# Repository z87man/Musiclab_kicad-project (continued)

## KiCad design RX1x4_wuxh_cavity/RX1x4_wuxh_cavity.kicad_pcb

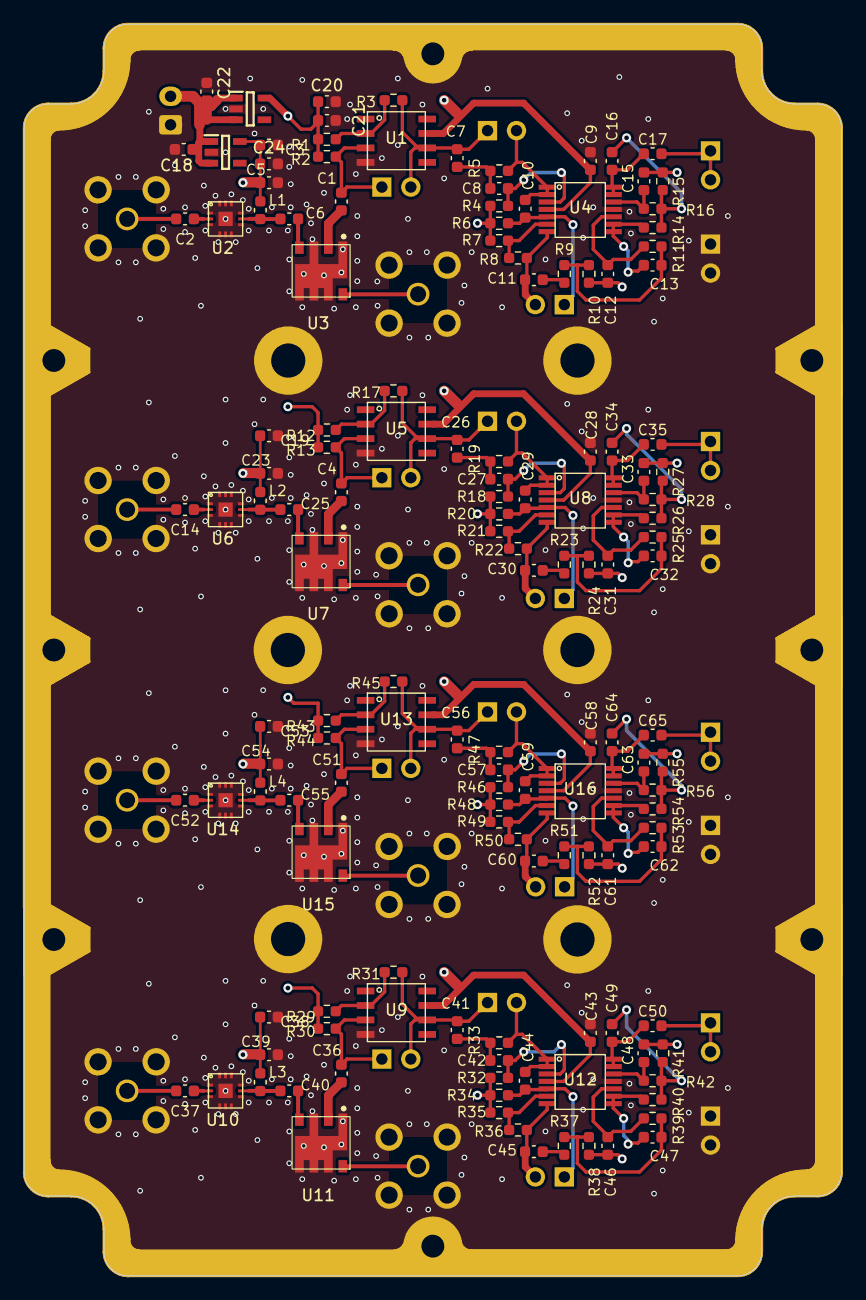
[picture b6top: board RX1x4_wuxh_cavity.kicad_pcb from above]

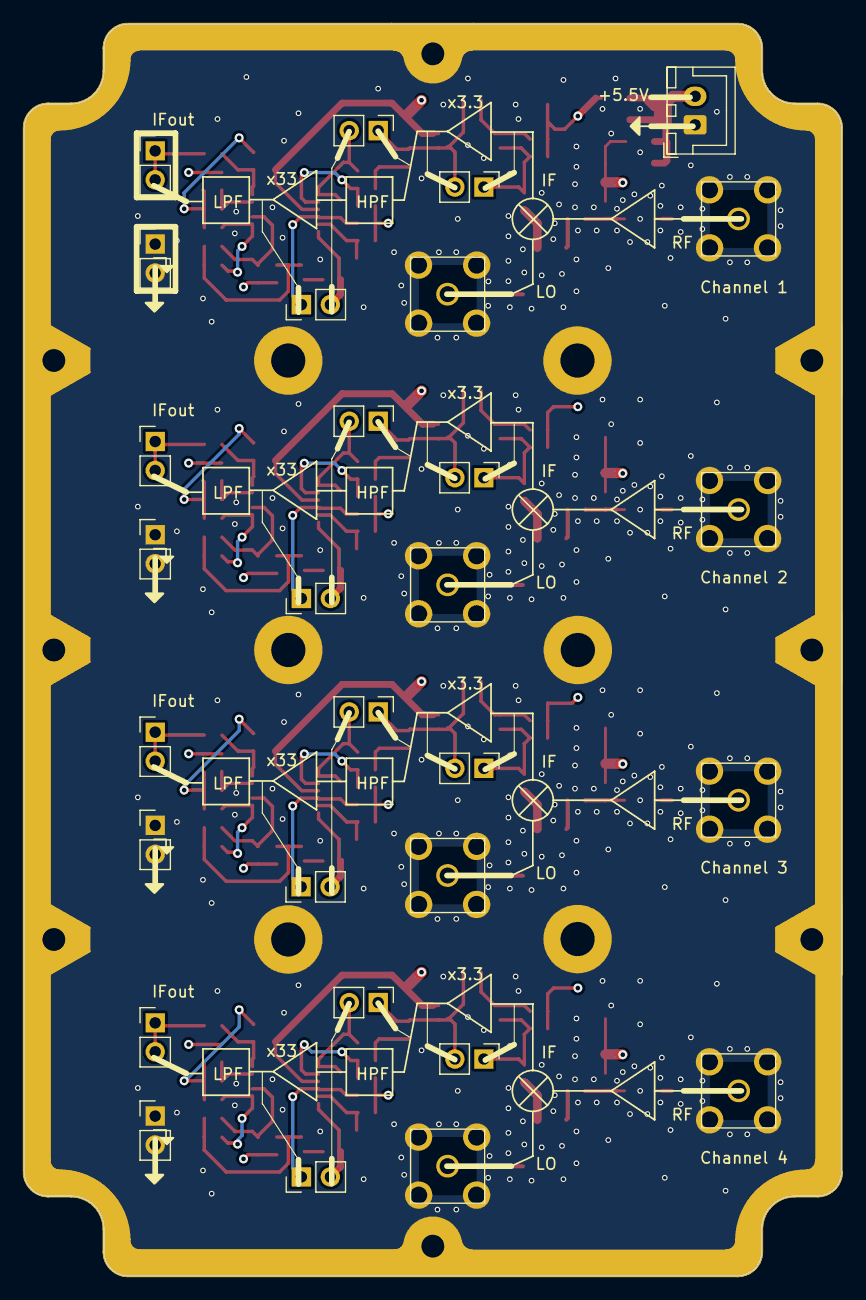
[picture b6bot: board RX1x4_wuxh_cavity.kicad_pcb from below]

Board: 4 copper layers, 71.7 x 109.8 mm, 173 parts (29 on the bottom side), 96 nets.

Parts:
C1, C4, C10, C11, C17, C29, C30, C35, C36, C44, C45, C50, C51, C59, C60, C65: 1u; C_0603_1608Metric_revised
C2, C6, C14, C25, C37, C40, C52, C55: 22 uF; C_0603_1608Metric_revised
C3, C19, C38, C53: 4.7 uF; C_0603_1608Metric_revised
C5, C23, C39, C54: 1 nF; C_0603_1608Metric_revised
C7, C26, C41, C56: 200p; C_0603_1608Metric_revised
C8, C27, C42, C57: 110p; C_0603_1608Metric_revised
C9, C28, C43, C58: 2.2u; C_0603_1608Metric_revised
C12, C15, C31, C33, C46, C48, C61, C63: 100p; C_0603_1608Metric_revised
C13, C32, C47, C62: 120p; C_0603_1608Metric_revised
C16, C34, C49, C64: 750p; C_0603_1608Metric_revised
C18, C20, C22, C24: 1uf; C_0603_1608Metric_revised
C21: 4.7uF; C_0603_1608Metric_revised
IC1: TPS7A2025PDBVR; DC_SOT95P280X145-5N
IC2: TPS7A2050PDBVR; DC_SOT95P280X145-5N
J1, J2, J3, J5, J8, J9, J12, J13, J14, J17, J18, J19: Conn_01x02; PinHeader_1x02_P2.54mm_Vertical
J4: Conn_01x02_Pin; JST_XH_B2B-XH-A_1x02_P2.50mm_Vertical
J6, J7, J10, J11, J15, J16, J20, J21: Conn_01x02_Pin; PinHeader_1x02_P2.54mm_Vertical
L1, L2, L3, L4: 15 nH; L_0603_1608Metric_revised
R1, R2, R6, R7, R12, R13, R20, R21, R29, R30, R34, R35, R43, R44, R48, R49: 1k; R_0603_1608Metric_revised
R3, R17, R31, R45: 3.3k; R_0603_1608Metric_revised
R4, R18, R32, R46: 16k; R_0603_1608Metric_revised
R5, R19, R33, R47: 7.5k; R_0603_1608Metric_revised
R8, R22, R36, R50: 33k; R_0603_1608Metric_revised
R9, R23, R37, R51: 6.2k; R_0603_1608Metric_revised
R10, R15, R24, R27, R38, R41, R52, R55: 100k; R_0603_1608Metric_revised
R11, R25, R39, R53: 8.2k; R_0603_1608Metric_revised
R14, R26, R40, R54: 2.2k; R_0603_1608Metric_revised
R16, R28, R42, R56: 3.9k; R_0603_1608Metric_revised
SMA1, SMA2, SMA3, SMA4, SMA5, SMA6, SMA7, SMA8: SMA_KHD
U1, U5, U9, U13: OPA1611_SOIC8; OPA1611-SOIC8
U2, U6, U10, U14: PMA-63GLN+; PMA3-63GLN+
U3, U7, U11, U15: SIM73L
U4, U8, U12, U16: TL974IPWR
outline1: Outline_8x5_cavity_20230723(2mm)

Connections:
+2.5V: C12.2, C15.2, C20.1, C21.1, C31.2, C33.2, C46.2, C48.2, C61.2, C63.2, IC1.5 (OUT), R1.2, R2.2, R4.1, R6.2, R7.2, R10.2, R12.2, R13.2, R15.2, R18.1, R20.2, R21.2, R24.2, R27.2, R29.2, R30.2, R32.1, R34.2, R35.2, R38.2, R41.2, R43.2, R44.2, R46.1, R48.2, R49.2, R52.2, R55.2
+5V: C3.1, C5.1, C9.1, C19.1, C23.1, C24.1, C28.1, C38.1, C39.1, C43.1, C53.1, C54.1, C58.1, IC2.5 (OUT), L1.1, L2.1, L3.1, L4.1, U1.7 (V+), U4.4 (V+), U5.7 (V+), U8.4 (V+), U9.7 (V+), U12.4 (V+), U13.7 (V+), U16.4 (V+)
/RX_singleChannel1/IF: C4.1, U7.2 (IF)
/RX_singleChannel2/IF: C36.1, U11.2 (IF)
/RX_singleChannel3/IF: C51.1, U15.2 (IF)
/RX_singleChannel/IF: C1.1, U3.2 (IF)
GND: C3.2, C5.2, C9.2, C18.2, C19.2, C20.2, C21.2, C22.2, C23.2, C24.2, C28.2, C38.2, C39.2, C43.2, C53.2, C54.2, C58.2, IC1.2 (GND), IC2.2 (GND), J4.1, J7.1, J7.2, J11.1, J11.2, J16.1, J16.2, J21.1, J21.2, SMA1.2, SMA2.2, SMA3.2, SMA4.2, SMA5.2, SMA6.2, SMA7.2, SMA8.2, U1.4 (V-), U2.1 (NC), U2.3 (NC), U2.4 (NC), U2.5 (NC), U2.6 (NC), U2.7 (NC), U2.9 (NC), U2.10 (NC), U2.11 (NC), U2.12 (NC), U2.13 (EP), U3.1 (GND), U3.3 (GND), U3.5 (GND), U3.6 (GND), U3.7 (GND), U3.9 (GND), U4.11 (V-), U5.4 (V-), U6.1 (NC), U6.3 (NC), U6.4 (NC), U6.5 (NC), U6.6 (NC), U6.7 (NC), U6.9 (NC), U6.10 (NC), U6.11 (NC), U6.12 (NC), U6.13 (EP), U7.1 (GND), U7.3 (GND), U7.5 (GND), U7.6 (GND), U7.7 (GND), U7.9 (GND), U8.11 (V-), U9.4 (V-), U10.1 (NC), U10.3 (NC), U10.4 (NC), U10.5 (NC), U10.6 (NC), U10.7 (NC), U10.9 (NC), U10.10 (NC), U10.11 (NC), U10.12 (NC), U10.13 (EP), U11.1 (GND), U11.3 (GND), U11.5 (GND), U11.6 (GND), U11.7 (GND), U11.9 (GND), U12.11 (V-), U13.4 (V-), U14.1 (NC), U14.3 (NC), U14.4 (NC), U14.5 (NC), U14.6 (NC), U14.7 (NC), U14.9 (NC), U14.10 (NC), U14.11 (NC), U14.12 (NC), U14.13 (EP), U15.1 (GND), U15.3 (GND), U15.5 (GND), U15.6 (GND), U15.7 (GND), U15.9 (GND), U16.11 (V-), outline1.1 (GND)
unnamed: C2.1, SMA1.1
unnamed: C7.2, C8.1, R5.1
unnamed: C11.2, R9.1
unnamed: C12.1, R11.2, U4.10 (In)
unnamed: C13.1, R9.2, R10.1, R11.1
unnamed: C14.1, SMA3.1
unnamed: C15.1, R16.2, U4.12 (In)
unnamed: C16.1, R14.2, R15.1, R16.1
unnamed: C26.2, C27.1, R19.1
unnamed: C30.2, R23.1
unnamed: C31.1, R25.2, U8.10 (In)
unnamed: C32.1, R23.2, R24.1, R25.1
unnamed: C33.1, R28.2, U8.12 (In)
unnamed: C34.1, R26.2, R27.1, R28.1
unnamed: C37.1, SMA5.1
unnamed: C41.2, C42.1, R33.1
unnamed: C45.2, R37.1
unnamed: C46.1, R39.2, U12.10 (In)
unnamed: C47.1, R37.2, R38.1, R39.1
unnamed: C48.1, R42.2, U12.12 (In)
unnamed: C49.1, R40.2, R41.1, R42.1
unnamed: C52.1, SMA7.1
unnamed: C56.2, C57.1, R47.1
unnamed: C60.2, R51.1
unnamed: C61.1, R53.2, U16.10 (In)
unnamed: C62.1, R51.2, R52.1, R53.1
unnamed: C63.1, R56.2, U16.12 (In)
unnamed: C64.1, R54.2, R55.1, R56.1
unnamed: C1.2, J1.1, R2.1, U1.3 (in+)
unnamed: C7.1, J1.2, J2.1, R3.2, U1.6 (Out)
unnamed: C10.1, J2.2, R5.2, U4.1 (Out), U4.2 (in-)
unnamed: C10.2, J3.1, R6.1, U4.5 (In)
unnamed: C11.1, J3.2, R8.2, U4.7 (Out)
unnamed: C4.2, J5.1, R13.1, U5.3 (in+)
unnamed: C26.1, J5.2, J8.1, R17.2, U5.6 (Out)
unnamed: C17.2, J6.1, J6.2
unnamed: C29.1, J8.2, R19.2, U8.1 (Out), U8.2 (in-)
unnamed: C29.2, J9.1, R20.1, U8.5 (In)
unnamed: C30.1, J9.2, R22.2, U8.7 (Out)
unnamed: C35.2, J10.1, J10.2
unnamed: C36.2, J12.1, R30.1, U9.3 (in+)
unnamed: C41.1, J12.2, J13.1, R31.2, U9.6 (Out)
unnamed: C44.1, J13.2, R33.2, U12.1 (Out), U12.2 (in-)
unnamed: C44.2, J14.1, R34.1, U12.5 (In)
unnamed: C45.1, J14.2, R36.2, U12.7 (Out)
unnamed: C50.2, J15.1, J15.2
unnamed: C51.2, J17.1, R44.1, U13.3 (in+)
unnamed: C56.1, J17.2, J18.1, R45.2, U13.6 (Out)
unnamed: C59.1, J18.2, R47.2, U16.1 (Out), U16.2 (in-)
unnamed: C59.2, J19.1, R48.1, U16.5 (In)
unnamed: C60.1, J19.2, R50.2, U16.7 (Out)
unnamed: C65.2, J20.1, J20.2
unnamed: R7.1, R8.1, U4.6 (In)
unnamed: R21.1, R22.1, U8.6 (In)
unnamed: R35.1, R36.1, U12.6 (In)
unnamed: R49.1, R50.1, U16.6 (In)
unnamed: R1.1, R3.1, U1.2 (in-)
unnamed: C2.2, U2.2 (RFin)
unnamed: C6.1, L1.2, U2.8 (RFout&DCin)
unnamed: SMA2.1, U3.8 (LO)
unnamed: C6.2, U3.4 (RF)
unnamed: C8.2, R4.2, U4.3 (in+)
unnamed: C13.2, R14.1, U4.8 (Out), U4.9 (In)
unnamed: C16.2, C17.1, U4.13 (In), U4.14 (Out)
unnamed: R12.1, R17.1, U5.2 (in-)
unnamed: C14.2, U6.2 (RFin)
unnamed: C25.1, L2.2, U6.8 (RFout&DCin)
unnamed: SMA4.1, U7.8 (LO)
unnamed: C25.2, U7.4 (RF)
unnamed: C27.2, R18.2, U8.3 (in+)
unnamed: C32.2, R26.1, U8.8 (Out), U8.9 (In)
unnamed: C34.2, C35.1, U8.13 (In), U8.14 (Out)
unnamed: R29.1, R31.1, U9.2 (in-)
unnamed: C37.2, U10.2 (RFin)
unnamed: C40.1, L3.2, U10.8 (RFout&DCin)
unnamed: SMA6.1, U11.8 (LO)
unnamed: C40.2, U11.4 (RF)
unnamed: C42.2, R32.2, U12.3 (in+)
unnamed: C47.2, R40.1, U12.8 (Out), U12.9 (In)
unnamed: C49.2, C50.1, U12.13 (In), U12.14 (Out)
unnamed: R43.1, R45.1, U13.2 (in-)
unnamed: C52.2, U14.2 (RFin)
unnamed: C55.1, L4.2, U14.8 (RFout&DCin)
unnamed: SMA8.1, U15.8 (LO)
unnamed: C55.2, U15.4 (RF)
unnamed: C57.2, R46.2, U16.3 (in+)
unnamed: C62.2, R54.1, U16.8 (Out), U16.9 (In)
unnamed: C64.2, C65.1, U16.13 (In), U16.14 (Out)
Vin: C18.1, C22.1, IC1.1 (IN), IC1.3 (EN), IC2.1 (IN), IC2.3 (EN), J4.2

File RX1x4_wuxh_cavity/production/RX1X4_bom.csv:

Designator,Footprint,Quantity,Value,LCSC Part #
"C1, C10, C11, C17, C29, C30, C35, C36, C4, C44, C45, C50, C51, C59, C60, C65",0603,16,1u,
"C12, C15, C31, C33, C46, C48, C61, C63",0603,8,100p,
"C13, C32, C47, C62",0603,4,120p,
"C14, C2, C25, C37, C40, C52, C55, C6",0603,8,22 uF,
"C16, C34, C49, C64",0603,4,750p,
"C18, C20, C22, C24",0603,4,1uf,
"C19, C3, C38, C53",0603,4,4.7 uF,
C21,0603,1,4.7uF,
"C23, C39, C5, C54",0603,4,1 nF,
"C26, C41, C56, C7",0603,4,200p,
"C27, C42, C57, C8",0603,4,110p,
"C28, C43, C58, C9",0603,4,2.2u,
IC1,DC_SOT95P280X145-5N,1,TPS7A2025PDBVR,
IC2,DC_SOT95P280X145-5N,1,TPS7A2050PDBVR,
"J1, J12, J13, J14, J17, J18, J19, J2, J3, J5, J8, J9",PinHeader_1x02_P2.54mm_Vertical,12,Conn_01x02,
"J10, J11, J15, J16, J20, J21, J6, J7",PinHeader_1x02_P2.54mm_Vertical,8,Conn_01x02_Pin,
J4,JST_XH_B2B-XH-A_1x02_P2.50mm_Vertical,1,Conn_01x02_Pin,
"L1, L2, L3, L4",0603,4,15 nH,
"R1, R12, R13, R2, R20, R21, R29, R30, R34, R35, R43, R44, R48, R49, R6, R7",0603,16,1k,
"R10, R15, R24, R27, R38, R41, R52, R55",0603,8,100k,
"R11, R25, R39, R53",0603,4,8.2k,
"R14, R26, R40, R54",0603,4,2.2k,
"R16, R28, R42, R56",0603,4,3.9k,
"R17, R3, R31, R45",0603,4,3.3k,
"R18, R32, R4, R46",0603,4,16k,
"R19, R33, R47, R5",0603,4,7.5k,
"R22, R36, R50, R8",0603,4,33k,
"R23, R37, R51, R9",0603,4,6.2k,
"SMA1, SMA2, SMA3, SMA4, SMA5, SMA6, SMA7, SMA8",SMA_KHD,8,~,
"U1, U13, U5, U9",OPA1611-SOIC8,4,OPA1611_SOIC8,
"U10, U14, U2, U6",PMA3-63GLN+,4,PMA-63GLN+,
"U11, U15, U3, U7",SIM73L,4,~,
"U12, U16, U4, U8",TL974IPWR,4,~,
outline1,Outline_8x5_cavity_20230723(2mm),1,~,

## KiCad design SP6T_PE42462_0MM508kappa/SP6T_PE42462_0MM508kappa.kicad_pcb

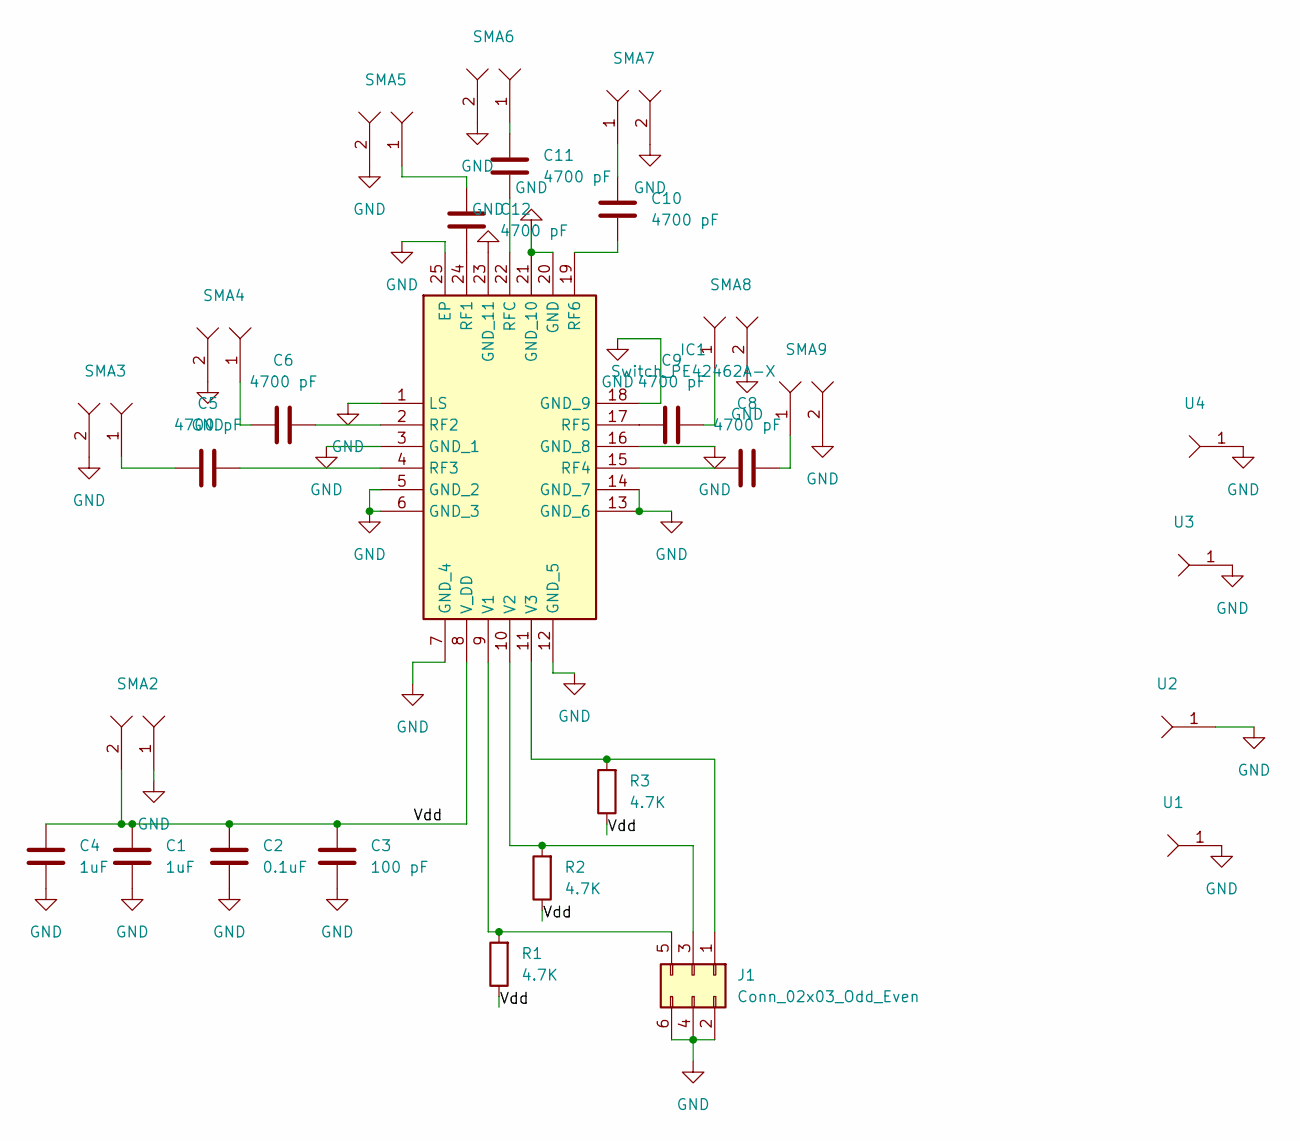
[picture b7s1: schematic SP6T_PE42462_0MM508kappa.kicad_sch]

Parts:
C1, C4: 1uF; C_0402_1005Metric
C2: 0.1uF; C_0402_1005Metric
C3: 100 pF; C_0402_1005Metric
C5, C6, C8, C9, C10, C11, C12: 4700 pF; C_0402_1005Metric
IC1: Switch_PE42462A-X; Switch_1p6t_PE42462_QFN50P400X400X90-25N-D; Mouser Part Number 81-PE42462A-X
J1: Conn_02x03_Odd_Even; PinHeader_2x03_P2.54mm_Vertical_SMD
R1, R2, R3: 4.7K; R_0402_1005Metric
SMA2: JST_EH_S2B-EH_1x02_P2.50mm_Horizontal
SMA3, SMA4, SMA5, SMA6, SMA7, SMA8, SMA9: SMA_Edge_step_1
U1, U2, U3, U4: via_GND

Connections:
/Vdd: C1.1, C2.1, C3.1, C4.1, IC1.8 (V_DD), R1.1, R2.1, R3.1, SMA2.2
GND: C1.2, C2.2, C3.2, C4.2, IC1.1 (LS), IC1.3 (GND_1), IC1.5 (GND_2), IC1.6 (GND_3), IC1.7 (GND_4), IC1.12 (GND_5), IC1.13 (GND_6), IC1.14 (GND_7), IC1.16 (GND_8), IC1.18 (GND_9), IC1.20 (GND), IC1.21 (GND_10), IC1.23 (GND_11), IC1.25 (EP), J1.2, J1.4, J1.6, SMA2.1, SMA3.2, SMA4.2, SMA5.2, SMA6.2, SMA7.2, SMA8.2, SMA9.2, U1.1, U2.1, U3.1, U4.1
unnamed: C5.1, SMA3.1
unnamed: C6.1, SMA4.1
unnamed: C8.2, SMA9.1
unnamed: C9.2, SMA8.1
unnamed: C10.2, SMA7.1
unnamed: C11.2, SMA6.1
unnamed: C12.2, SMA5.1
unnamed: C12.1, IC1.24 (RF1)
unnamed: C6.2, IC1.2 (RF2)
unnamed: C5.2, IC1.4 (RF3)
unnamed: C8.1, IC1.15 (RF4)
unnamed: C9.1, IC1.17 (RF5)
unnamed: C10.1, IC1.19 (RF6)
unnamed: C11.1, IC1.22 (RFC)
unnamed: IC1.9 (V1), J1.5, R1.2
unnamed: IC1.10 (V2), J1.3, R2.2
unnamed: IC1.11 (V3), J1.1, R3.2

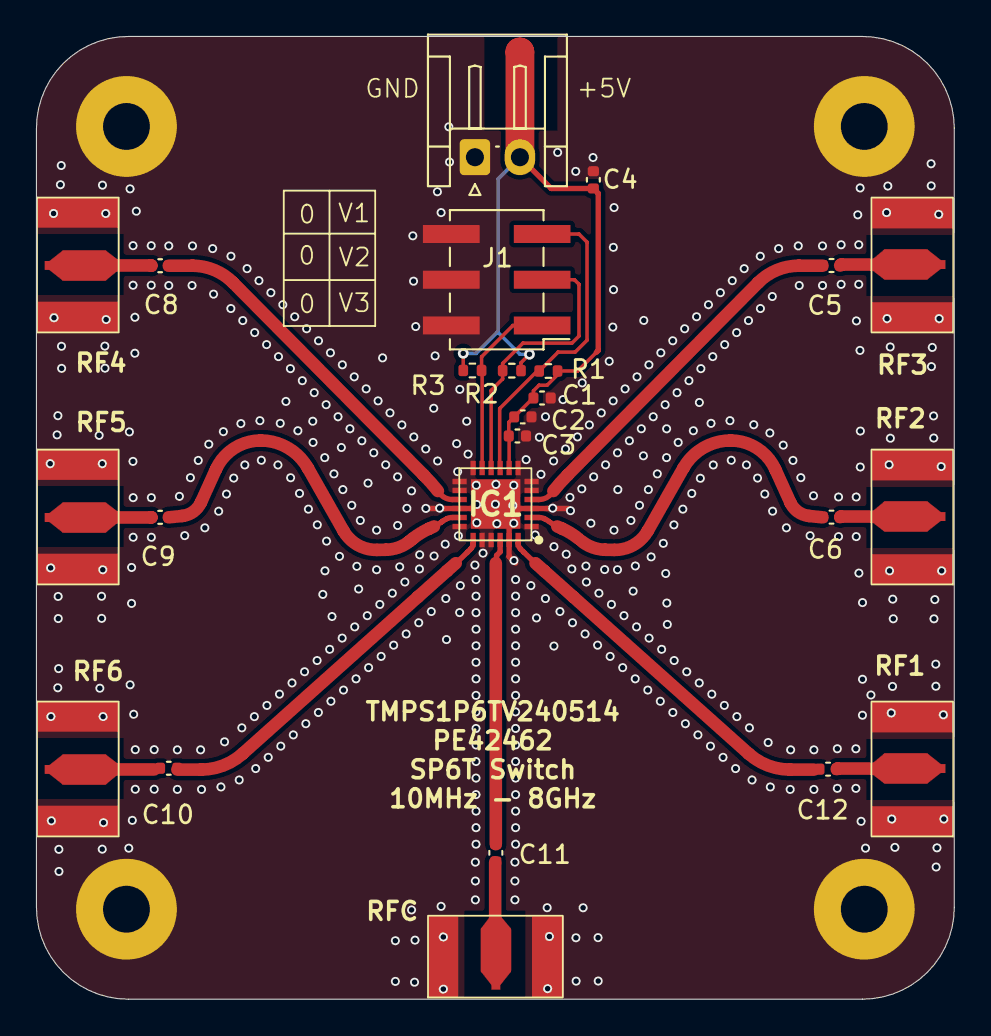
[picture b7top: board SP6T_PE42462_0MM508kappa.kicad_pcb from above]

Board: 2 copper layers, 51.0 x 53.5 mm, 28 parts (0 on the bottom side), 19 nets.

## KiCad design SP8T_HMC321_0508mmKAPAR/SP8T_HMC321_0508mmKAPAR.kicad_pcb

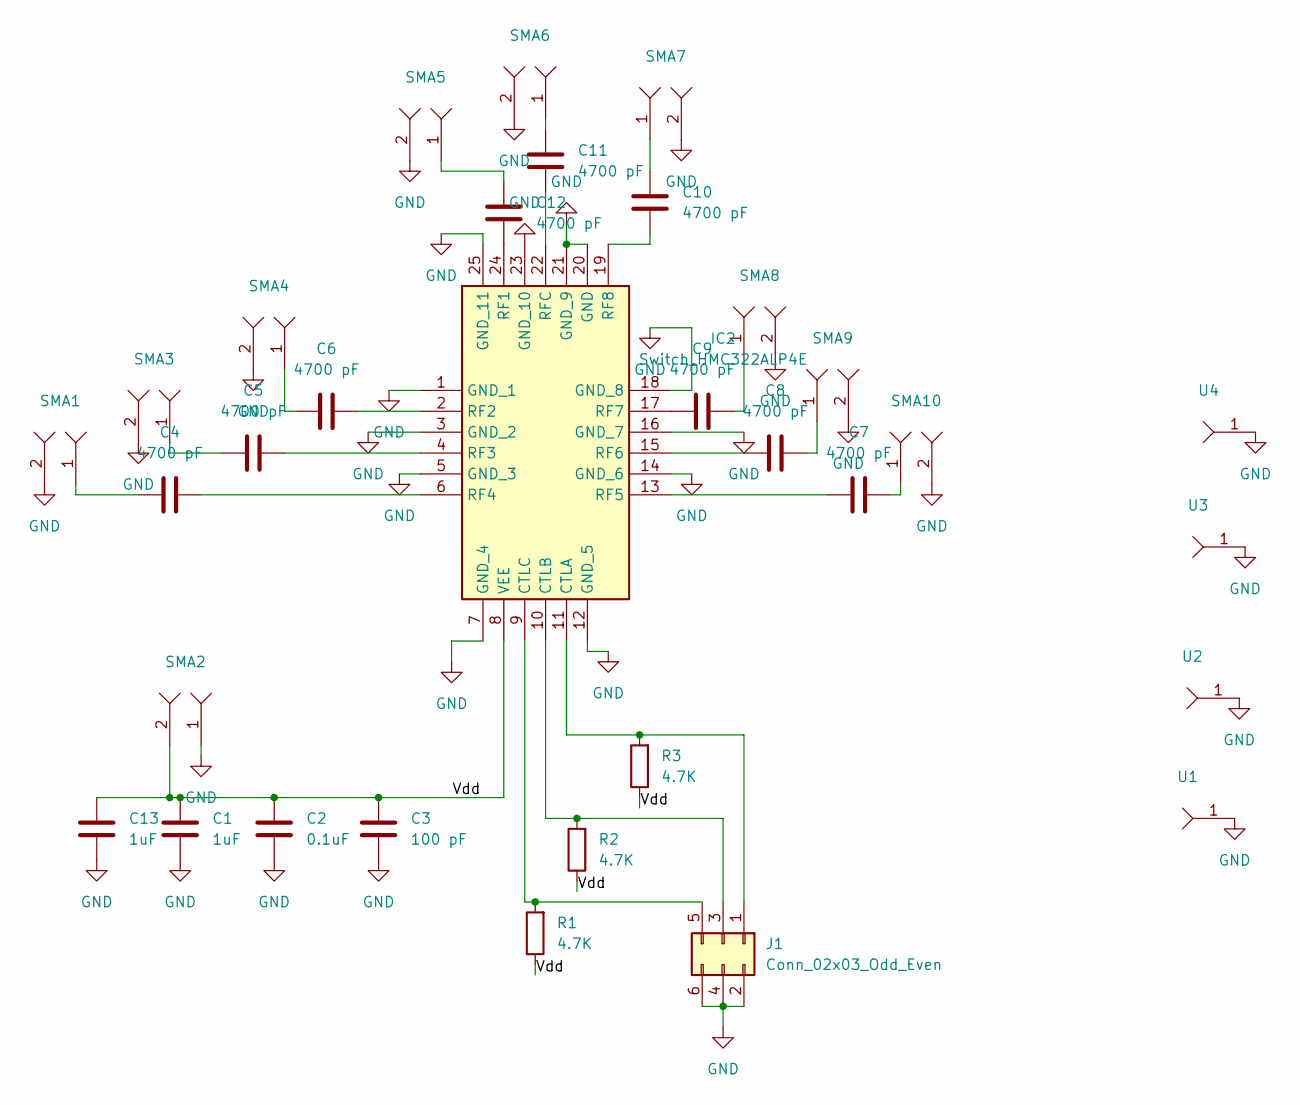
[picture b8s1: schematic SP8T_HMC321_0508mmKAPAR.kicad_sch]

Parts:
C1, C13: 1uF; C_0402_1005Metric
C2: 0.1uF; C_0402_1005Metric
C3: 100 pF; C_0402_1005Metric
C4, C5, C6, C7, C8, C9, C10, C11, C12: 4700 pF; C_0402_1005Metric
IC2: Switch_HMC322ALP4E; Switch_HMC321_QFN50P400X400X90-25N-D; Mouser Part Number 584-HMC322ALP4E
J1: Conn_02x03_Odd_Even; PinHeader_2x03_P2.54mm_Vertical_SMD
R1, R2, R3: 4.7K; R_0402_1005Metric
SMA1, SMA3, SMA4, SMA5, SMA6, SMA7, SMA8, SMA9, SMA10: SMA_Edge_step_1
SMA2: JST_EH_S2B-EH_1x02_P2.50mm_Horizontal
U1, U2, U3, U4: via_GND

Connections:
/Vdd: C1.1, C2.1, C3.1, C13.1, IC2.8 (VEE), R1.1, R2.1, R3.1, SMA2.2
GND: C1.2, C2.2, C3.2, C13.2, IC2.1 (GND_1), IC2.3 (GND_2), IC2.5 (GND_3), IC2.7 (GND_4), IC2.12 (GND_5), IC2.14 (GND_6), IC2.16 (GND_7), IC2.18 (GND_8), IC2.20 (GND), IC2.21 (GND_9), IC2.23 (GND_10), IC2.25 (GND_11), J1.2, J1.4, J1.6, SMA1.2, SMA2.1, SMA3.2, SMA4.2, SMA5.2, SMA6.2, SMA7.2, SMA8.2, SMA9.2, SMA10.2, U1.1, U2.1, U3.1, U4.1
unnamed: C4.1, SMA1.1
unnamed: C5.1, SMA3.1
unnamed: C6.1, SMA4.1
unnamed: C7.2, SMA10.1
unnamed: C8.2, SMA9.1
unnamed: C9.2, SMA8.1
unnamed: C10.2, SMA7.1
unnamed: C11.2, SMA6.1
unnamed: C12.2, SMA5.1
unnamed: IC2.11 (CTLA), J1.1, R3.2
unnamed: IC2.10 (CTLB), J1.3, R2.2
unnamed: IC2.9 (CTLC), J1.5, R1.2
unnamed: C12.1, IC2.24 (RF1)
unnamed: C6.2, IC2.2 (RF2)
unnamed: C5.2, IC2.4 (RF3)
unnamed: C4.2, IC2.6 (RF4)
unnamed: C7.1, IC2.13 (RF5)
unnamed: C8.1, IC2.15 (RF6)
unnamed: C9.1, IC2.17 (RF7)
unnamed: C10.1, IC2.19 (RF8)
unnamed: C11.1, IC2.22 (RFC)

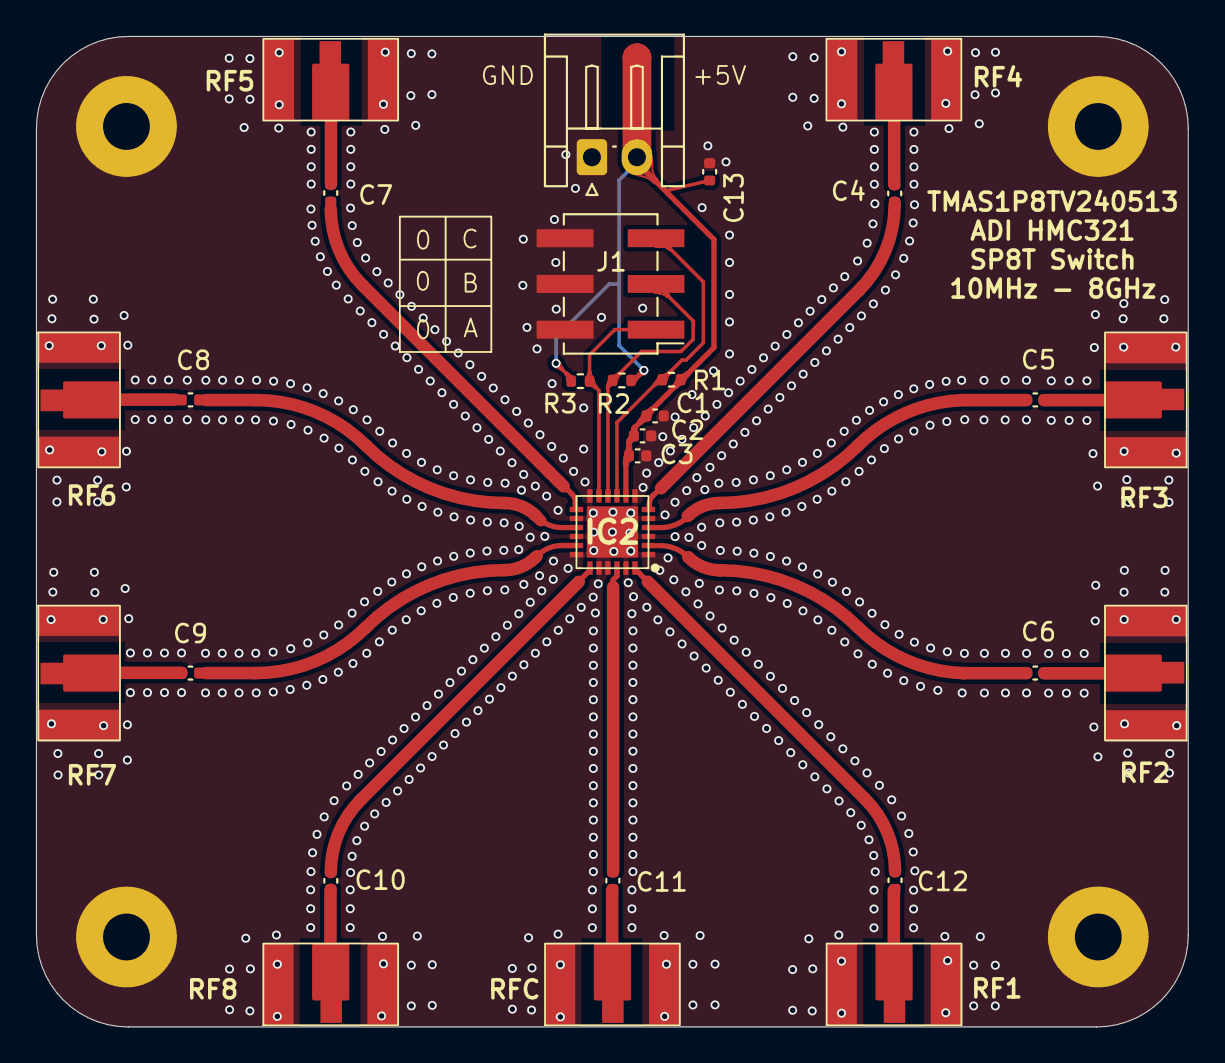
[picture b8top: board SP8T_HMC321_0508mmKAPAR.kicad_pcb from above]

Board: 2 copper layers, 64.0 x 55.0 mm, 32 parts (0 on the bottom side), 23 nets.
